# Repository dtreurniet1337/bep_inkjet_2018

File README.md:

# BEP Inkjet 2018
Repository for the inkjet BEP group of 2018

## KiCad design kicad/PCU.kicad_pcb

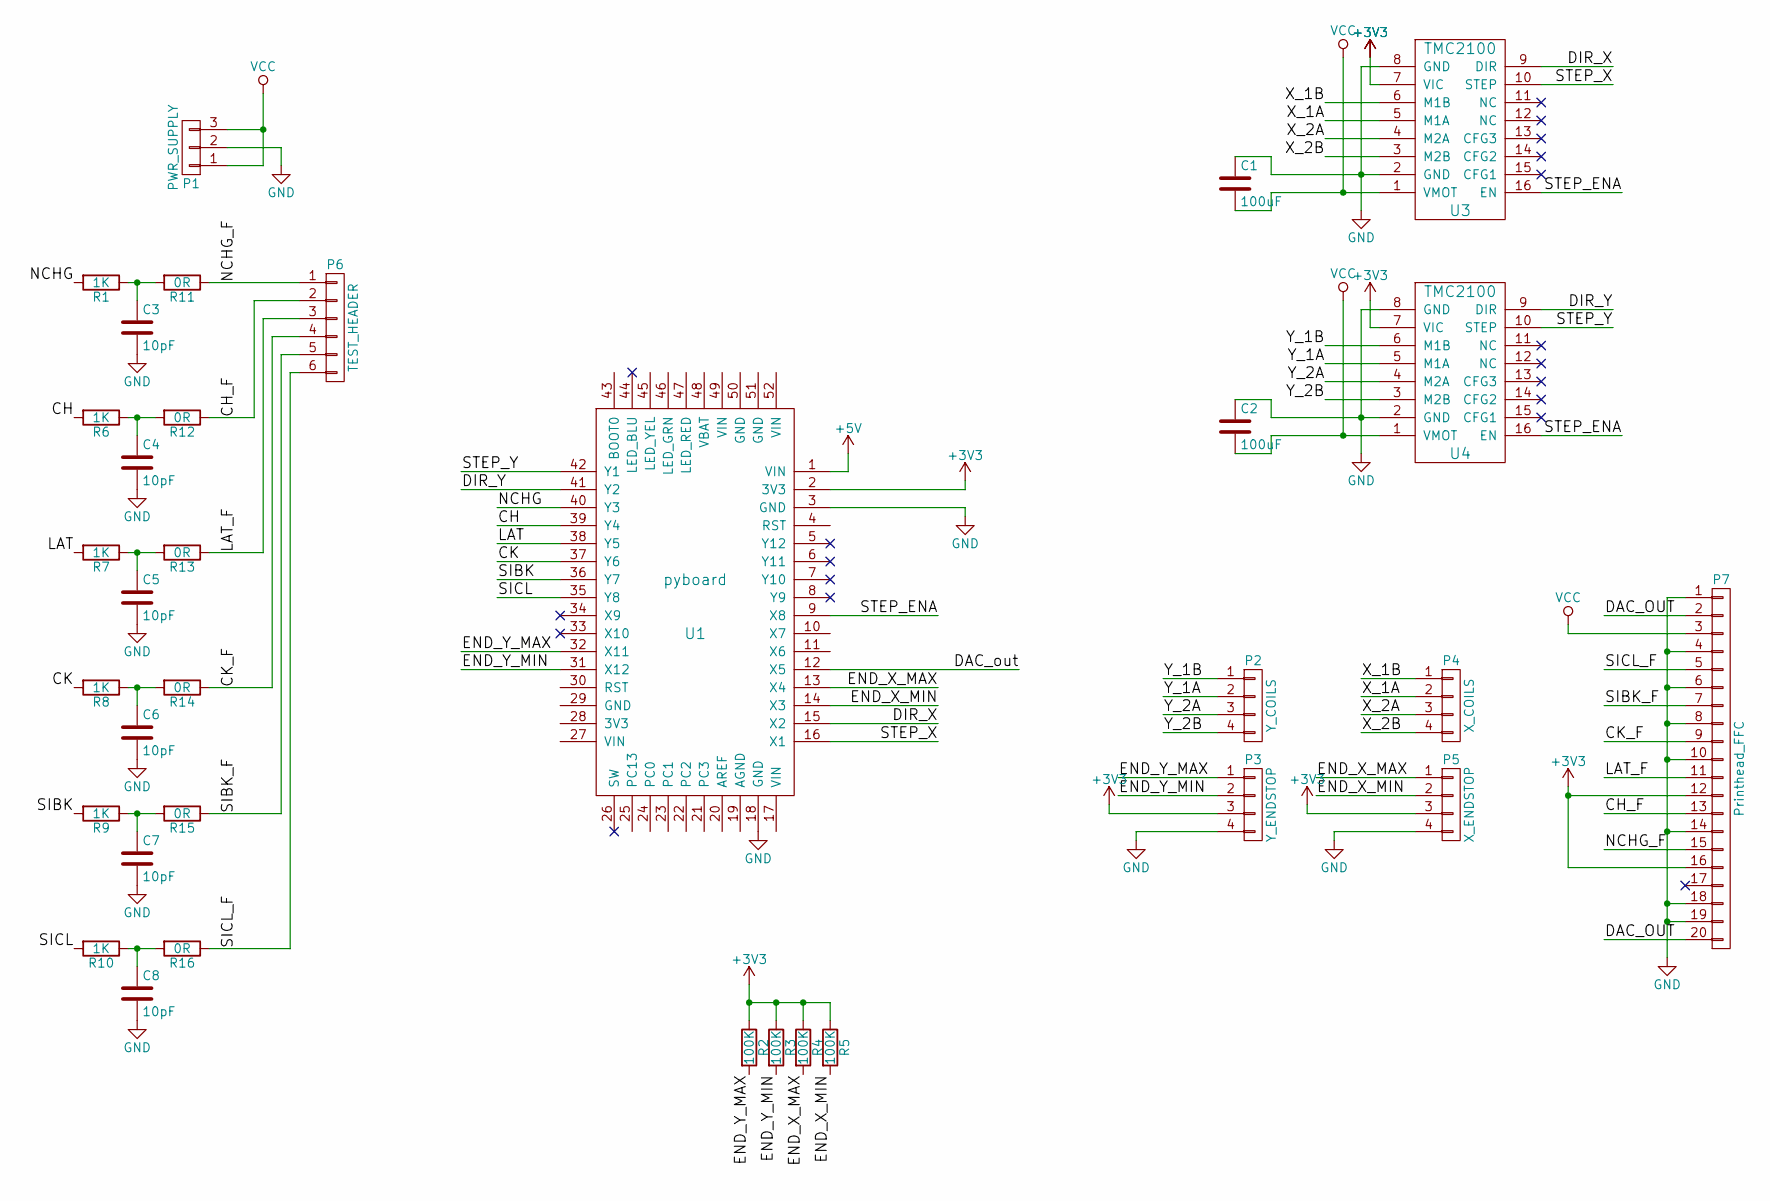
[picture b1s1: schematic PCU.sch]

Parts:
C1, C2: 100uF; Capacitor_D8_L11.5
C3, C4, C5, C6, C7, C8: 10pF; C_Disc_D3_P2.5
P1: PWR_SUPPLY; Pin_Header_Straight_1x03
P2: Y_COILS; Pin_Header_Straight_1x04
P3: Y_ENDSTOP; Pin_Header_Straight_1x04
P4: X_COILS; Pin_Header_Straight_1x04
P5: X_ENDSTOP; Pin_Header_Straight_1x04
P6: TEST_HEADER; Pin_Header_Straight_1x06
P7: Printhead_FFC; Pin_Header_Straight_1x20
R1, R6, R7, R8, R9, R10: 1K; Resistor_Horizontal_RM10mm
R2, R3, R4, R5: 100K; Resistor_Horizontal_RM10mm
R11, R12, R13, R14, R15, R16: 0R; Resistor_Horizontal_RM10mm
U1: pyboard; Pyboard
U3, U4: TMC2100

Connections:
+3V3: P3.3, P5.3, P7.12, P7.16, R2.1, R3.1, R4.1, R5.1, U1.2 (3V3), U3.7 (VIC), U4.7 (VIC)
/CH: R6.2, U1.39 (Y4)
/CH_F: P6.2, P7.13, R12.1
/CK: R8.2, U1.37 (Y6)
/CK_F: P6.4, P7.9, R14.1
/DAC_OUT: P7.2, P7.20, U1.12 (X5)
/DIR_X: U1.15 (X2), U3.9 (DIR)
/DIR_Y: U1.41 (Y2), U4.9 (DIR)
/END_X_MAX: P5.1, R4.2, U1.13 (X4)
/END_X_MIN: P5.2, R5.2, U1.14 (X3)
/END_Y_MAX: P3.1, R2.2, U1.32 (X11)
/END_Y_MIN: P3.2, R3.2, U1.31 (X12)
/LAT: R7.2, U1.38 (Y5)
/LAT_F: P6.3, P7.11, R13.1
/NCHG: R1.2, U1.40 (Y3)
/NCHG_F: P6.1, P7.15, R11.1
/SIBK: R9.2, U1.36 (Y7)
/SIBK_F: P6.5, P7.7, R15.1
/SICL: R10.2, U1.35 (Y8)
/SICL_F: P6.6, P7.5, R16.1
/STEP_ENA: U1.9 (X8), U3.16 (EN), U4.16 (EN)
/STEP_X: U1.16 (X1), U3.10 (STEP)
/STEP_Y: U1.42 (Y1), U4.10 (STEP)
/X_1A: P4.2, U3.5 (M1A)
/X_1B: P4.1, U3.6 (M1B)
/X_2A: P4.3, U3.4 (M2A)
/X_2B: P4.4, U3.3 (M2B)
/Y_1A: P2.2, U4.5 (M1A)
/Y_1B: P2.1, U4.6 (M1B)
/Y_2A: P2.3, U4.4 (M2A)
/Y_2B: P2.4, U4.3 (M2B)
GND: C1.1, C2.1, C3.2, C4.2, C5.2, C6.2, C7.2, C8.2, P1.2, P3.4, P5.4, P7.1, P7.4, P7.6, P7.8, P7.10, P7.14, P7.18, P7.19, U1.3 (GND), U1.18 (GND), U3.2 (GND), U3.8 (GND), U4.2 (GND), U4.8 (GND)
unnamed: C3.1, R1.1, R11.2
unnamed: C4.1, R6.1, R12.2
unnamed: C5.1, R7.1, R13.2
unnamed: C6.1, R8.1, R14.2
unnamed: C7.1, R9.1, R15.2
unnamed: C8.1, R10.1, R16.2
VCC: C1.2, C2.2, P1.1, P1.3, P7.3, U3.1 (VMOT), U4.1 (VMOT)

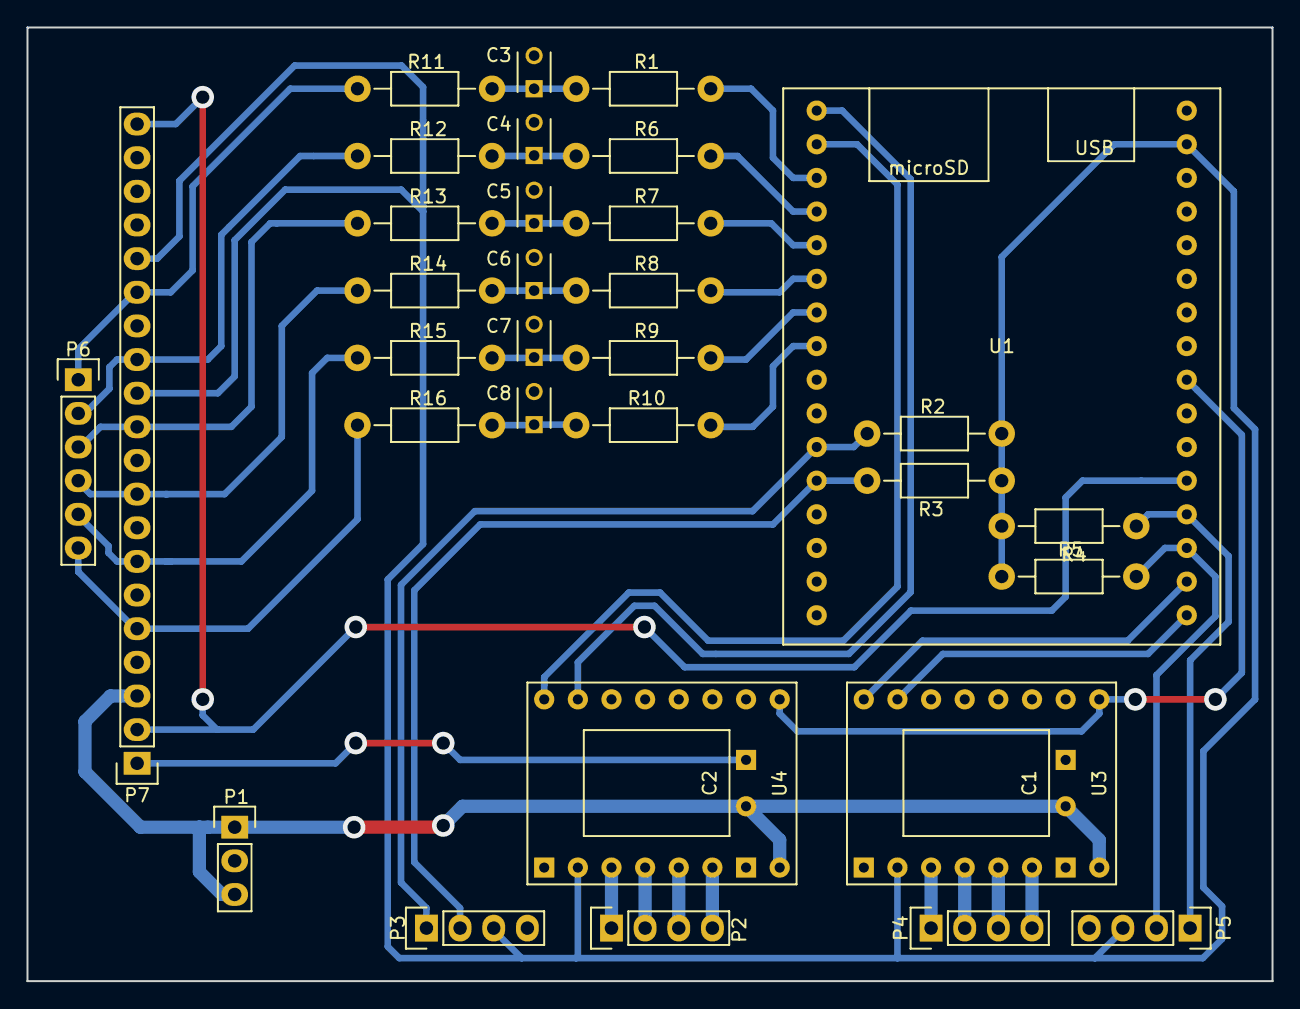
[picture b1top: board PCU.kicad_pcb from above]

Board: 2 copper layers, 94.0 x 72.0 mm, 34 parts (0 on the bottom side), 39 nets.

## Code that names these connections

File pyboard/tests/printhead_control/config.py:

################## Pin definitions ###################

STEP_ENA =      'X8'

# X stage
X_DIR =         'X1'
X_STEP =        'X2'
X_END_MIN =     'X4'
X_END_MAX =     'X3'

# Y stage
Y_DIR =         'Y1'
Y_STEP =        'Y2'
Y_END_MIN =     'X12'
Y_END_MAX =     'X11'


# LV printhead logic
SICL =          'Y3'
SIBL =          'Y4'
CK =            'Y5'
LAT =           'Y6'
CH =            'Y7'
NCHG =          'Y8'

# GPIO addresses
GPIO_SICL =          8
GPIO_SIBL =          9
GPIO_CK =            12
GPIO_LAT =           13
GPIO_CH =            14
GPIO_NCHG =          15

# DAC
DAC =           'X5'


###################### MISC #########################

STAGE_MICROSTEPPING = 16
STAGE_RANGE = (100, 100) #mm
STAGE_PITCH = 1 #mm
STAGE_STEPS_PER_REV = 200
STAGE_STEP_DELAY = 500 #us


################## Settings ##########################
ENABLE_ENDSTOPS = False

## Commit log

2018-06-22 Amazing
2018-07-06 Final
